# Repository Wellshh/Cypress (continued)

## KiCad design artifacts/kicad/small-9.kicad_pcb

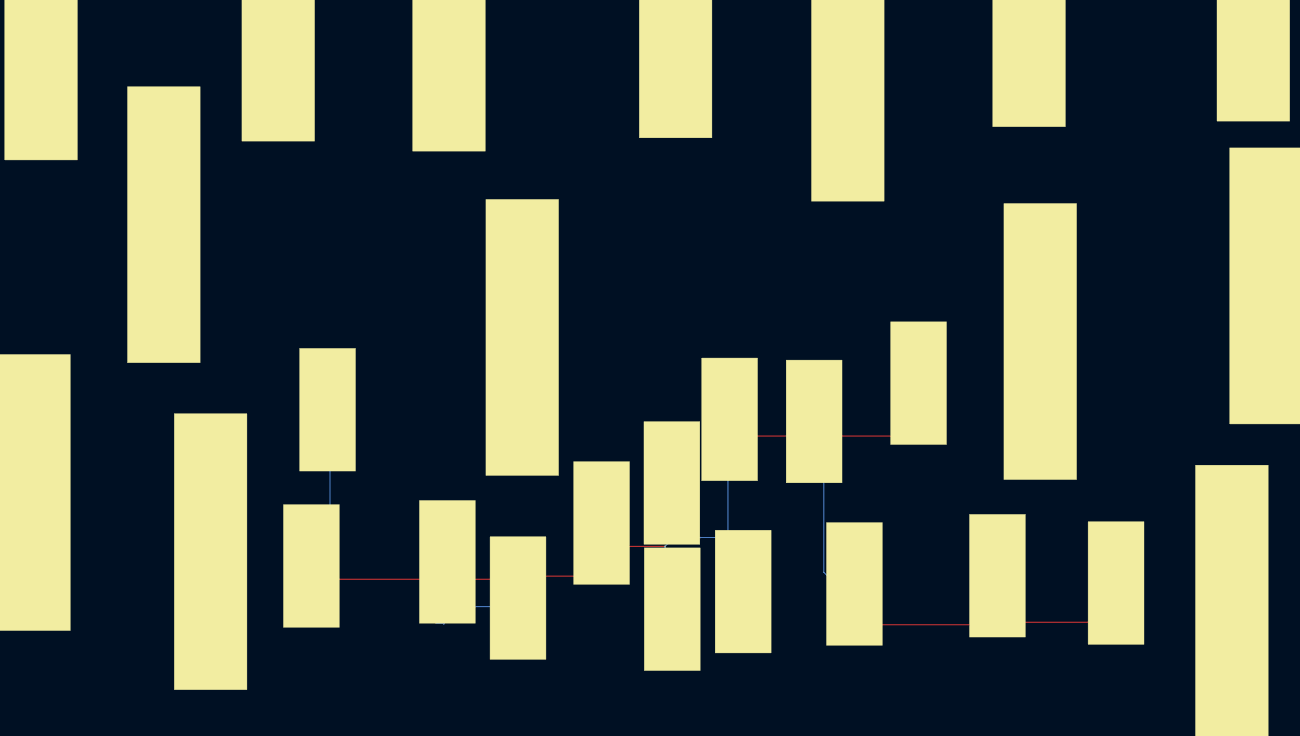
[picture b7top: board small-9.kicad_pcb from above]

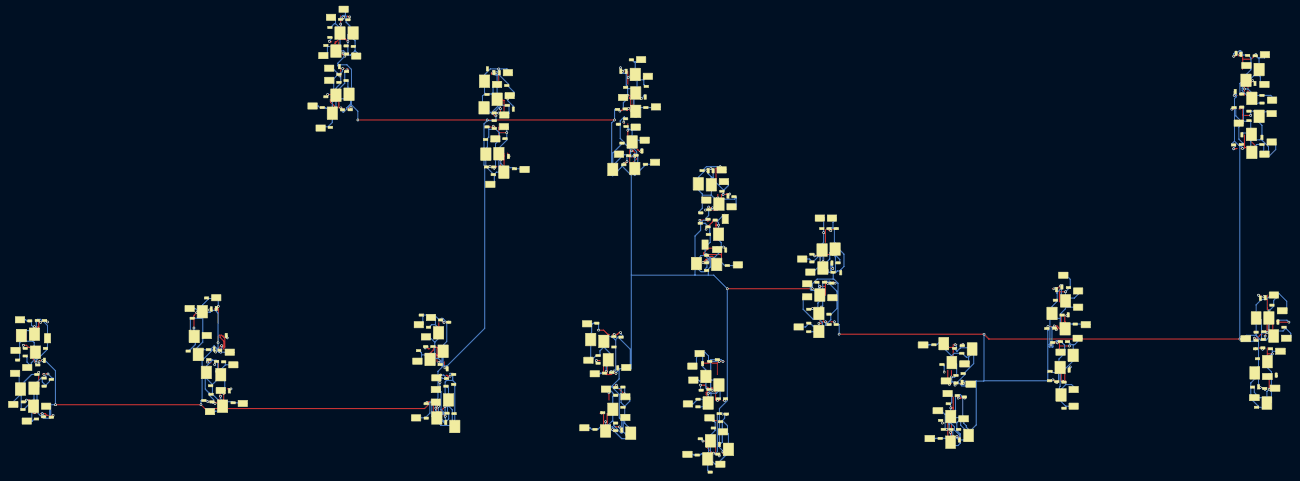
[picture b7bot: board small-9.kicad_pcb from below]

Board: 2 copper layers, 476 parts (448 on the bottom side), 252 nets.

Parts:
C77: C77
C78: C78
C79: C79
C80: C80
C81: C81
C82: C82
C83: C83
C84: C84
C85: C85
C86: C86
C87: C87
C88: C88
C89: C89
C90: C90
C91: C91
C92: C92
C93: C93
C94: C94
C95: C95
C96: C96
C97: C97
C98: C98
C106: C106
C107: C107
C108: C108
C109: C109
C110: C110
C111: C111
C112: C112
C113: C113
C120: C120
C121: C121
C122: C122
C129: C129
C131: C131
C133: C133
C135: C135
C136: C136
C140: C140
C141: C141
C142: C142
C144: C144
C146: C146
C148: C148
C150: C150
C151: C151
C153: C153
C155: C155
C177: C177
C178: C178
C179: C179
C196: C196
C197: C197
C198: C198
C199: C199
C200: C200
C201: C201
C202: C202
C203: C203
C204: C204
C205: C205
C206: C206
C222: C222
C223: C223
C224: C224
C225: C225
C228: C228
C331: C331
C332: C332
C333: C333
C334: C334
C335: C335
C336: C336
C337: C337
C338: C338
C339: C339
C340: C340
C341: C341
C342: C342
C343: C343
C344: C344
C345: C345
C346: C346
C347: C347
C348: C348
C349: C349
C350: C350
C351: C351
C352: C352
C353: C353
C354: C354
C355: C355
C356: C356
C357: C357
C358: C358
C359: C359
C360: C360
C361: C361
C362: C362
C363: C363
C364: C364
C365: C365
C366: C366
C367: C367
C368: C368
C369: C369
C370: C370
C371: C371
C372: C372
C373: C373
C374: C374
C375: C375
C376: C376
C377: C377
C378: C378
C379: C379
C380: C380
C381: C381
C382: C382
C383: C383
C384: C384
C385: C385
C386: C386
C387: C387
C388: C388
C389: C389
C390: C390
C391: C391
C392: C392
C393: C393
C394: C394
C396: C396
C397: C397
C398: C398
C400: C400
C401: C401
C403: C403
C404: C404
C405: C405
C406: C406
C407: C407
C408: C408
C409: C409
C411: C411
C413: C413
C415: C415
C417: C417
C419: C419
C420: C420
C421: C421
C422: C422
C423: C423
C424: C424
C425: C425
C426: C426
C427: C427
C428: C428
C429: C429
C430: C430
C431: C431
C432: C432
C433: C433
C434: C434
C435: C435
C436: C436
C437: C437
C438: C438
C439: C439
C440: C440
C441: C441
C442: C442
C443: C443
C444: C444
C445: C445
C446: C446
C447: C447
C448: C448
C449: C449
C450: C450
C451: C451
C452: C452
C453: C453
C4279: C4279
C4280: C4280
C4281: C4281
C4282: C4282
C4283: C4283
C4284: C4284
C4285: C4285
C4286: C4286
C4287: C4287
C4288: C4288
C4289: C4289
C4290: C4290
C4291: C4291
C4292: C4292
C4293: C4293
C4294: C4294
C4295: C4295
C4296: C4296
C4297: C4297
C4298: C4298
C4299: C4299
C4300: C4300
C4301: C4301
C4302: C4302
C4303: C4303
C4304: C4304
C4305: C4305
C4306: C4306
C4307: C4307
C4308: C4308
C4309: C4309
C4310: C4310
C4311: C4311
C4312: C4312
C4313: C4313
C4314: C4314
C4315: C4315
C4316: C4316
C4317: C4317
C4318: C4318
C4319: C4319
C4320: C4320
J103: J103
J104: J104
J105: J105
J106: J106
J107: J107
J108: J108
J109: J109
J110: J110
J111: J111
J112: J112
J113: J113
J114: J114
J115: J115
J116: J116
J203: J203
J204: J204
J205: J205
J206: J206
J207: J207
J208: J208
J209: J209
J210: J210
J211: J211
J212: J212
J213: J213
J214: J214
J215: J215
J216: J216
L37: L37
L38: L38
L39: L39
L40: L40
L41: L41
L42: L42
L43: L43
L44: L44
L45: L45
L46: L46
L47: L47
L48: L48
L49: L49
L50: L50
L51: L51
L52: L52
L53: L53
L54: L54
L55: L55
L56: L56
L57: L57
L58: L58
L59: L59
L60: L60
L61: L61
L62: L62
L63: L63
L64: L64
L65: L65
L68: L68
L69: L69
L70: L70
L71: L71
L72: L72
L73: L73
L74: L74
L75: L75
L76: L76
L77: L77
L78: L78
L79: L79
L80: L80
L81: L81
L82: L82
L83: L83
L84: L84
L85: L85
L86: L86
L87: L87
L88: L88
L89: L89
L90: L90
L91: L91
L92: L92
L93: L93
L94: L94
L95: L95
L96: L96
L97: L97
L98: L98
L99: L99
L100: L100
L101: L101
L102: L102
L103: L103
L104: L104
L105: L105
L106: L106
L107: L107
L108: L108
L109: L109
L110: L110
L111: L111
L112: L112
L113: L113
L114: L114
L115: L115
L116: L116
L117: L117
L118: L118
L119: L119
L120: L120
L121: L121
L122: L122
R230: R230
R231: R231
R232: R232
R233: R233
R234: R234
R235: R235
R236: R236
R237: R237
R238: R238
R239: R239
R240: R240
R241: R241
R242: R242
R243: R243
R244: R244
R245: R245
R246: R246
R247: R247
R248: R248
R249: R249
R250: R250
R251: R251
R252: R252
R253: R253
R254: R254
R255: R255
R256: R256
R257: R257
R258: R258
R259: R259
R260: R260
R261: R261
R262: R262
R263: R263
R264: R264
R265: R265
R266: R266
R267: R267
R268: R268
R269: R269
R270: R270
R271: R271
R272: R272
R273: R273
R274: R274
R275: R275
R280: R280
R283: R283
R284: R284
R285: R285
R293: R293
R294: R294
R295: R295
R296: R296
R297: R297
R298: R298
R299: R299
R300: R300
R301: R301
R302: R302
R303: R303
R304: R304
R305: R305
R306: R306
R307: R307
R308: R308
R309: R309
R310: R310
R311: R311
R312: R312
R313: R313
R314: R314
R315: R315
R316: R316
R317: R317
R318: R318
R319: R319
R320: R320
R321: R321
R322: R322
R323: R323
R324: R324
R325: R325
R326: R326
R327: R327
R328: R328
R329: R329
R330: R330
R331: R331
R332: R332
R333: R333
R334: R334
R335: R335
R336: R336
R337: R337
R338: R338
R339: R339
R340: R340
R341: R341
R342: R342
R343: R343
R345: R345
R347: R347
R349: R349
R350: R350
R351: R351
R352: R352
R353: R353
R357: R357
R358: R358
R359: R359
R360: R360
R361: R361
R362: R362
R363: R363
R370: R370
R379: R379
R380: R380
R381: R381
R382: R382
R383: R383
R386: R386
R387: R387
R388: R388
R389: R389
R390: R390
R391: R391
R392: R392
R393: R393
R394: R394
R395: R395
R425: R425
R426: R426
R427: R427
R428: R428
R429: R429
R438: R438
R439: R439
R444: R444
R445: R445

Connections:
GP_EPPS_P05: J103.12, R233.0
GP_EPPS_P06: J103.13, R231.0
GP_EPPS_P07: J104.12, R241.0
GP_EPPS_P08: J104.13, R243.0
GP_EPPS_P09: J105.12, R253.0
GP_EPPS_P10: J105.13, R251.0
GP_EPPS_P11: J106.12, R261.0
GP_EPPS_P12: J106.13, R263.0
GP_EPPS_P13: J107.12, R273.0
GP_EPPS_P14: J107.13, R271.0
GP_EPPS_P15: J108.12, R294.0
GP_EPPS_P16: J108.13, R296.0
GP_EPPS_P17: J109.12, R306.0
GP_EPPS_P18: J109.13, R304.0
GP_EPPS_P19: J110.12, R314.0
GP_EPPS_P20: J110.13, R316.0
GP_EPPS_P21: J111.12, R326.0
GP_EPPS_P22: J111.13, R324.0
GP_EPPS_P23: J112.12, R334.0
GP_EPPS_P24: J112.13, R336.0
GP_EPPS_P25: J113.12, R349.0
GP_EPPS_P26: J113.13, R345.0
GP_EPPS_P27: J114.12, R360.0
GP_EPPS_P28: J114.13, R362.0
GP_EPPS_P29: J115.12, R388.0
GP_EPPS_P30: J115.13, R386.0
GP_EPPS_P31: J116.12, R425.0
GP_EPPS_P32: J116.13, R427.0
GP_INT_P05_L: J103.14, R239.1
GP_INT_P06_L: J103.15, R238.1
GP_INT_P07_L: J104.14, R248.1
GP_INT_P08_L: J104.15, R249.1
GP_INT_P09_L: J105.14, R259.1
GP_INT_P10_L: J105.15, R258.1
GP_INT_P11_L: J106.14, R268.1
GP_INT_P12_L: J106.15, R269.1
GP_INT_P13_L: J107.14, R285.1
GP_INT_P14_L: J107.15, R284.1
GP_INT_P15_L: J108.14, R301.1
GP_INT_P16_L: J108.15, R302.1
GP_INT_P17_L: J109.14, R312.1
GP_INT_P18_L: J109.15, R311.1
GP_INT_P19_L: J110.14, R321.1
GP_INT_P20_L: J110.15, R322.1
GP_INT_P21_L: J111.14, R332.1
GP_INT_P22_L: J111.15, R331.1
GP_INT_P23_L: J112.14, R341.1
GP_INT_P24_L: J112.15, R342.1
GP_INT_P25_L: J113.14, R358.1
GP_INT_P26_L: J113.15, R357.1
GP_INT_P27_L: J114.14, R381.1
GP_INT_P28_L: J114.15, R382.1
GP_INT_P29_L: J115.14, R394.1
GP_INT_P30_L: J115.15, R393.1
GP_INT_P31_L: J116.14, R444.1
GP_INT_P32_L: J116.15, R445.1
GP_MOD_PRST_P05_L: J103.18, R232.1
GP_MOD_PRST_P06_L: J103.19, R230.1
GP_MOD_PRST_P07_L: J104.18, R240.1
GP_MOD_PRST_P08_L: J104.19, R242.1
GP_MOD_PRST_P09_L: J105.18, R252.1
GP_MOD_PRST_P10_L: J105.19, R250.1
GP_MOD_PRST_P11_L: J106.18, R260.1
GP_MOD_PRST_P12_L: J106.19, R262.1
GP_MOD_PRST_P13_L: J107.18, R272.1
GP_MOD_PRST_P14_L: J107.19, R270.1
GP_MOD_PRST_P15_L: J108.18, R293.1
GP_MOD_PRST_P16_L: J108.19, R295.1
GP_MOD_PRST_P17_L: J109.18, R305.1
GP_MOD_PRST_P18_L: J109.19, R303.1
GP_MOD_PRST_P19_L: J110.18, R313.1
GP_MOD_PRST_P20_L: J110.19, R315.1
GP_MOD_PRST_P21_L: J111.18, R325.1
GP_MOD_PRST_P22_L: J111.19, R323.1
GP_MOD_PRST_P23_L: J112.18, R333.1
GP_MOD_PRST_P24_L: J112.19, R335.1
GP_MOD_PRST_P25_L: J113.18, R347.1
GP_MOD_PRST_P26_L: J113.19, R343.1
GP_MOD_PRST_P27_L: J114.18, R359.1
GP_MOD_PRST_P28_L: J114.19, R361.1
GP_MOD_PRST_P29_L: J115.18, R387.1
GP_MOD_PRST_P30_L: J115.19, R383.1
GP_MOD_PRST_P31_L: J116.18, R395.1
GP_MOD_PRST_P32_L: J116.19, R426.1
I2C_SCL_QSFPDD_P05: J103.84, R235.1
I2C_SCL_QSFPDD_P06: J103.85, R234.1
I2C_SCL_QSFPDD_P07: J104.84, R244.1
I2C_SCL_QSFPDD_P08: J104.85, R245.1
I2C_SCL_QSFPDD_P09: J105.84, R255.1
I2C_SCL_QSFPDD_P10: J105.85, R254.1
I2C_SCL_QSFPDD_P11: J106.84, R264.1
I2C_SCL_QSFPDD_P12: J106.85, R265.1
I2C_SCL_QSFPDD_P13: J107.84, R275.1
I2C_SCL_QSFPDD_P14: J107.85, R274.1
I2C_SCL_QSFPDD_P15: J108.84, R297.1
I2C_SCL_QSFPDD_P16: J108.85, R298.1
I2C_SCL_QSFPDD_P17: J109.84, R308.1
I2C_SCL_QSFPDD_P18: J109.85, R307.1
I2C_SCL_QSFPDD_P19: J110.84, R317.1
I2C_SCL_QSFPDD_P20: J110.85, R318.1
I2C_SCL_QSFPDD_P21: J111.84, R328.1
I2C_SCL_QSFPDD_P22: J111.85, R327.1
I2C_SCL_QSFPDD_P23: J112.84, R337.1
I2C_SCL_QSFPDD_P24: J112.85, R338.1
I2C_SCL_QSFPDD_P25: J113.84, R351.1
I2C_SCL_QSFPDD_P26: J113.85, R350.1
I2C_SCL_QSFPDD_P27: J114.84, R363.1
I2C_SCL_QSFPDD_P28: J114.85, R370.1
I2C_SCL_QSFPDD_P29: J115.84, R390.1
I2C_SCL_QSFPDD_P30: J115.85, R389.1
I2C_SCL_QSFPDD_P31: J116.84, R428.1
I2C_SCL_QSFPDD_P32: J116.85, R429.1
I2C_SDA_QSFPDD_P05: J103.86, R237.1
I2C_SDA_QSFPDD_P06: J103.87, R236.1
I2C_SDA_QSFPDD_P07: J104.86, R246.1
I2C_SDA_QSFPDD_P08: J104.87, R247.1
I2C_SDA_QSFPDD_P09: J105.86, R257.1
I2C_SDA_QSFPDD_P10: J105.87, R256.1
I2C_SDA_QSFPDD_P11: J106.86, R266.1
I2C_SDA_QSFPDD_P12: J106.87, R267.1
I2C_SDA_QSFPDD_P13: J107.86, R283.1
I2C_SDA_QSFPDD_P14: J107.87, R280.1
I2C_SDA_QSFPDD_P15: J108.86, R299.1
I2C_SDA_QSFPDD_P16: J108.87, R300.1
I2C_SDA_QSFPDD_P17: J109.86, R310.1
I2C_SDA_QSFPDD_P18: J109.87, R309.1
I2C_SDA_QSFPDD_P19: J110.86, R319.1
I2C_SDA_QSFPDD_P20: J110.87, R320.1
I2C_SDA_QSFPDD_P21: J111.86, R330.1
I2C_SDA_QSFPDD_P22: J111.87, R329.1
I2C_SDA_QSFPDD_P23: J112.86, R339.1
I2C_SDA_QSFPDD_P24: J112.87, R340.1
I2C_SDA_QSFPDD_P25: J113.86, R353.1
I2C_SDA_QSFPDD_P26: J113.87, R352.1
I2C_SDA_QSFPDD_P27: J114.86, R379.1
I2C_SDA_QSFPDD_P28: J114.87, R380.1
I2C_SDA_QSFPDD_P29: J115.86, R392.1
I2C_SDA_QSFPDD_P30: J115.87, R391.1
I2C_SDA_QSFPDD_P31: J116.86, R438.1
I2C_SDA_QSFPDD_P32: J116.87, R439.1
NET_3.3V_VCC_P06: C83.0, C89.0, J103.2, J103.3, L39.0, R234.0, R236.0, R238.0
NET_3.3V_VCC_P07: C106.0, C112.0, J104.0, J104.1, L45.0, R244.0, R246.0, R248.0
NET_3.3V_VCC_P08: C109.0, C121.0, J104.2, J104.3, L48.0, R245.0, R247.0, R249.0
NET_3.3V_VCC_P09: C144.0, C155.0, J105.0, J105.1, L54.0, R255.0, R257.0, R259.0
NET_3.3V_VCC_P10: C140.0, C150.0, J105.2, J105.3, L51.0, R254.0, R256.0, R258.0
NET_3.3V_VCC_P11: C199.0, C205.0, J106.0, J106.1, L57.0, R264.0, R266.0, R268.0
NET_3.3V_VCC_P12: C202.0, C223.0, J106.2, J106.3, L60.0, R265.0, R267.0, R269.0
NET_3.3V_VCC_P13: C4285.0, C4291.0, J107.0, J107.1, L68.0, R275.0, R283.0, R285.0
NET_3.3V_VCC_P14: C4282.0, C4288.0, J107.2, J107.3, L63.0, R274.0, R280.0, R284.0
NET_3.3V_VCC_P15: C4298.0, C4304.0, J108.0, J108.1, L71.0, R297.0, R299.0, R301.0
NET_3.3V_VCC_P16: C4301.0, C4307.0, J108.2, J108.3, L74.0, R298.0, R300.0, R302.0
NET_3.3V_VCC_P17: C334.0, C340.0, J109.0, J109.1, L80.0, R308.0, R310.0, R312.0
NET_3.3V_VCC_P18: C331.0, C337.0, J109.2, J109.3, L77.0, R307.0, R309.0, R311.0
NET_3.3V_VCC_P19: C347.0, C353.0, J110.0, J110.1, L83.0, R317.0, R319.0, R321.0
NET_3.3V_VCC_P20: C350.0, C356.0, J110.2, J110.3, L86.0, R318.0, R320.0, R322.0
NET_3.3V_VCC_P21: C366.0, C372.0, J111.0, J111.1, L92.0, R328.0, R330.0, R332.0
NET_3.3V_VCC_P22: C363.0, C369.0, J111.2, J111.3, L89.0, R327.0, R329.0, R331.0
NET_3.3V_VCC_P23: C379.0, C385.0, J112.0, J112.1, L95.0, R337.0, R339.0, R341.0
NET_3.3V_VCC_P24: C382.0, C388.0, J112.2, J112.3, L98.0, R338.0, R340.0, R342.0
NET_3.3V_VCC_P25: C405.0, C4314.0, J113.0, J113.1, L104.0, R351.0, R353.0, R358.0
NET_3.3V_VCC_P26: C396.0, C4315.0, J113.2, J113.3, L101.0, R350.0, R352.0, R357.0
NET_3.3V_VCC_P27: C4317.0, C4320.0, J114.0, J114.1, L107.0, R363.0, R379.0, R381.0
NET_3.3V_VCC_P28: C415.0, C421.0, J114.2, J114.3, L110.0, R370.0, R380.0, R382.0
NET_3.3V_VCC_P29: C431.0, C437.0, J115.0, J115.1, L116.0, R390.0, R392.0, R394.0
NET_3.3V_VCC_P30: C428.0, C434.0, J115.2, J115.3, L113.0, R389.0, R391.0, R393.0
NET_3.3V_VCC_P31: C444.0, C450.0, J116.0, J116.1, L119.0, R428.0, R438.0, R444.0
NET_3.3V_VCC_P32: C447.0, C453.0, J116.2, J116.3, L122.0, R429.0, R439.0, R445.0
NET_3.3V_VCC_RX_P05: C84.0, C90.0, J103.4, J103.5, L40.0
NET_3.3V_VCC_RX_P06: C81.0, C87.0, J103.6, J103.7, L37.0
NET_3.3V_VCC_RX_P07: C97.0, C110.0, J104.4, J104.5, L43.0
NET_3.3V_VCC_RX_P08: C107.0, C113.0, J104.6, J104.7, L46.0
NET_3.3V_VCC_RX_P09: C141.0, C151.0, J105.4, J105.5, L52.0
NET_3.3V_VCC_RX_P10: C135.0, C146.0, J105.6, J105.7, L49.0
NET_3.3V_VCC_RX_P11: C197.0, C203.0, J106.4, J106.5, L55.0
NET_3.3V_VCC_RX_P12: C200.0, C206.0, J106.6, J106.7, L58.0
NET_3.3V_VCC_RX_P13: C4283.0, C4289.0, J107.4, J107.5, L64.0
NET_3.3V_VCC_RX_P14: C4280.0, C4286.0, J107.6, J107.7, L61.0
NET_3.3V_VCC_RX_P15: C4296.0, C4302.0, J108.4, J108.5, L69.0
NET_3.3V_VCC_RX_P16: C4299.0, C4305.0, J108.6, J108.7, L72.0
NET_3.3V_VCC_RX_P17: C332.0, C338.0, J109.4, J109.5, L78.0
NET_3.3V_VCC_RX_P18: C335.0, C4312.0, J109.6, J109.7, L75.0
NET_3.3V_VCC_RX_P19: C345.0, C351.0, J110.4, J110.5, L81.0
NET_3.3V_VCC_RX_P20: C348.0, C354.0, J110.6, J110.7, L84.0
NET_3.3V_VCC_RX_P21: C364.0, C370.0, J111.4, J111.5, L90.0
NET_3.3V_VCC_RX_P22: C361.0, C367.0, J111.6, J111.7, L87.0
NET_3.3V_VCC_RX_P23: C377.0, C383.0, J112.4, J112.5, L93.0
NET_3.3V_VCC_RX_P24: C380.0, C386.0, J112.6, J112.7, L96.0
NET_3.3V_VCC_RX_P25: C397.0, C403.0, J113.4, J113.5, L102.0
NET_3.3V_VCC_RX_P26: C393.0, C400.0, J113.6, J113.7, L99.0
NET_3.3V_VCC_RX_P27: C4316.0, C4319.0, J114.4, J114.5, L105.0
NET_3.3V_VCC_RX_P28: C413.0, C419.0, J114.6, J114.7, L108.0
NET_3.3V_VCC_RX_P29: C429.0, C435.0, J115.4, J115.5, L114.0
NET_3.3V_VCC_RX_P30: C426.0, C432.0, J115.6, J115.7, L111.0
NET_3.3V_VCC_RX_P31: C442.0, C448.0, J116.4, J116.5, L117.0
NET_3.3V_VCC_RX_P32: C445.0, C451.0, J116.6, J116.7, L120.0
NET_3.3V_VCC_TX_P05: C85.0, C91.0, J103.8, J103.9, L41.0
NET_3.3V_VCC_TX_P06: C82.0, C88.0, J103.10, J103.11, L38.0
NET_3.3V_VCC_TX_P07: C98.0, C111.0, J104.8, J104.9, L44.0
NET_3.3V_VCC_TX_P08: C108.0, C120.0, J104.10, J104.11, L47.0
NET_3.3V_VCC_TX_P09: C142.0, C153.0, J105.8, J105.9, L53.0
NET_3.3V_VCC_TX_P10: C136.0, C148.0, J105.10, J105.11, L50.0
NET_3.3V_VCC_TX_P11: C198.0, C204.0, J106.8, J106.9, L56.0
NET_3.3V_VCC_TX_P12: C201.0, C222.0, J106.10, J106.11, L59.0
NET_3.3V_VCC_TX_P13: C4284.0, C4290.0, J107.8, J107.9, L65.0
NET_3.3V_VCC_TX_P14: C4281.0, C4287.0, J107.10, J107.11, L62.0
NET_3.3V_VCC_TX_P15: C4297.0, C4303.0, J108.8, J108.9, L70.0
NET_3.3V_VCC_TX_P16: C4300.0, C4306.0, J108.10, J108.11, L73.0
NET_3.3V_VCC_TX_P17: C333.0, C339.0, J109.8, J109.9, L79.0
NET_3.3V_VCC_TX_P18: C336.0, C4313.0, J109.10, J109.11, L76.0
NET_3.3V_VCC_TX_P19: C346.0, C352.0, J110.8, J110.9, L82.0
NET_3.3V_VCC_TX_P20: C349.0, C355.0, J110.10, J110.11, L85.0
NET_3.3V_VCC_TX_P21: C365.0, C371.0, J111.8, J111.9, L91.0
NET_3.3V_VCC_TX_P22: C362.0, C368.0, J111.10, J111.11, L88.0
NET_3.3V_VCC_TX_P23: C378.0, C384.0, J112.8, J112.9, L94.0
NET_3.3V_VCC_TX_P24: C381.0, C387.0, J112.10, J112.11, L97.0
NET_3.3V_VCC_TX_P25: C398.0, C404.0, J113.8, J113.9, L103.0
NET_3.3V_VCC_TX_P26: C394.0, C401.0, J113.10, J113.11, L100.0
NET_3.3V_VCC_TX_P27: C411.0, C417.0, J114.8, J114.9, L106.0
NET_3.3V_VCC_TX_P28: C420.0, C4318.0, J114.10, J114.11, L109.0
NET_3.3V_VCC_TX_P29: C430.0, C436.0, J115.8, J115.9, L115.0
NET_3.3V_VCC_TX_P30: C427.0, C433.0, J115.10, J115.11, L112.0
NET_3.3V_VCC_TX_P31: C443.0, C449.0, J116.8, J116.9, L118.0
NET_3.3V_VCC_TX_P32: C446.0, C452.0, J116.10, J116.11, L121.0
NET_3V3_AUX: R230.0, R232.0, R240.0, R242.0, R250.0, R252.0, R260.0, R262.0, R270.0, R272.0, R293.0, R295.0, R303.0, R305.0, R313.0, R315.0, R323.0, R325.0, R333.0, R335.0, R343.0, R347.0, R359.0, R361.0, R383.0, R387.0, R395.0, R426.0
NET_3V3_P05: C78.0, C80.0, L40.1, L41.1, L42.1
NET_3V3_P06: C77.0, C79.0, L37.1, L38.1, L39.1
NET_3V3_P07: C93.0, C95.0, L43.1, L44.1, L45.1
NET_3V3_P08: C94.0, C96.0, L46.1, L47.1, L48.1
NET_3V3_P09: C129.0, C133.0, L52.1, L53.1, L54.1
NET_3V3_P10: C122.0, C131.0, L49.1, L50.1, L51.1
NET_3V3_P11: C177.0, C179.0, L55.1, L56.1, L57.1
NET_3V3_P12: C178.0, C196.0, L58.1, L59.1, L60.1
NET_3V3_P13: C225.0, C4279.0, L64.1, L65.1, L68.1
NET_3V3_P14: C224.0, C228.0, L61.1, L62.1, L63.1
NET_3V3_P15: C4292.0, C4294.0, L69.1, L70.1, L71.1
NET_3V3_P16: C4293.0, C4295.0, L72.1, L73.1, L74.1
NET_3V3_P17: C4309.0, C4311.0, L78.1, L79.1, L80.1
NET_3V3_P18: C4308.0, C4310.0, L75.1, L76.1, L77.1
NET_3V3_P19: C341.0, C343.0, L81.1, L82.1, L83.1
NET_3V3_P20: C342.0, C344.0, L84.1, L85.1, L86.1
NET_3V3_P21: C358.0, C360.0, L90.1, L91.1, L92.1
NET_3V3_P22: C357.0, C359.0, L87.1, L88.1, L89.1
NET_3V3_P23: C373.0, C375.0, L93.1, L94.1, L95.1
NET_3V3_P24: C374.0, C376.0, L96.1, L97.1, L98.1
NET_3V3_P25: C390.0, C392.0, L102.1, L103.1, L104.1
NET_3V3_P26: C389.0, C391.0, L99.1, L100.1, L101.1
NET_3V3_P27: C406.0, C408.0, L105.1, L106.1, L107.1
NET_3V3_P28: C407.0, C409.0, L108.1, L109.1, L110.1
NET_3V3_P29: C423.0, C425.0, L114.1, L115.1, L116.1
NET_3V3_P30: C422.0, C424.0, L111.1, L112.1, L113.1
NET_3V3_P31: C438.0, C440.0, L117.1, L118.1, L119.1
NET_3V3_P32: C439.0, C441.0, L120.1, L121.1, L122.1
